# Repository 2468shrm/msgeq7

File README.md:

# msgeq7

A PCB to interface an MSGEQ7 seven channel graphic equalizer IC to my smart sensor platform [link](https://github.com/2468shrm/M4_CAN_Feather_Carrier_v6). The board has a microphone input jack, the MSGEQ7 IC, and three 3-position square pin headers. One header for RESET, one for STROBE, and one for the analog OUTPUT.  These are connected to two DIOs and an AIN, respectively.

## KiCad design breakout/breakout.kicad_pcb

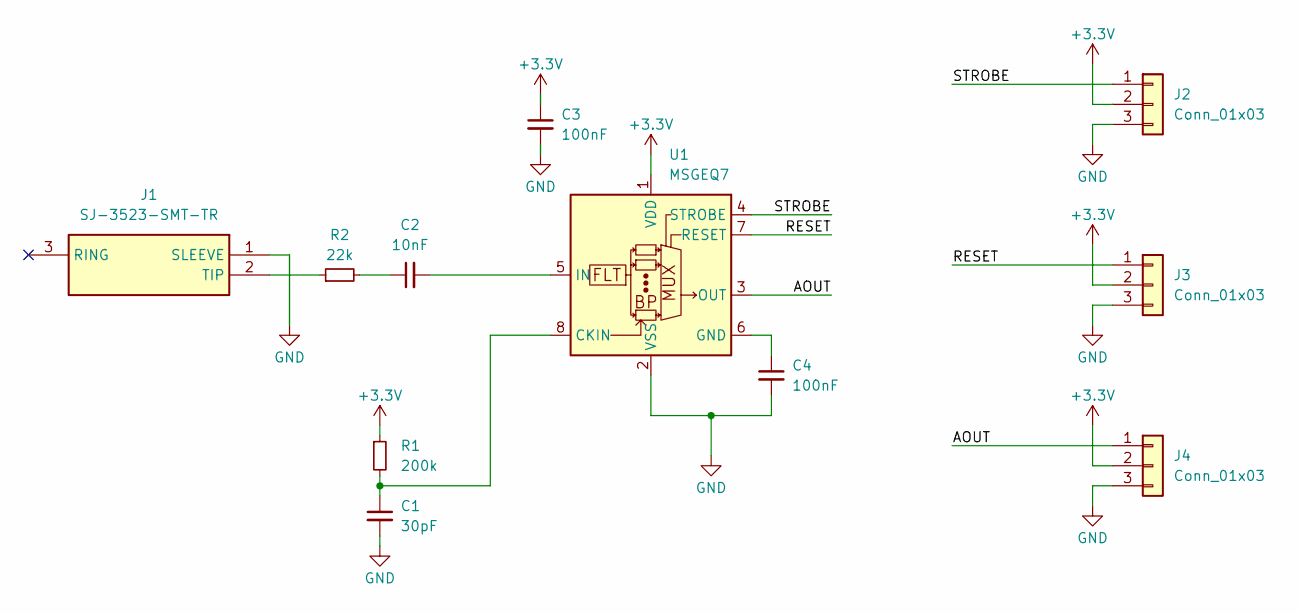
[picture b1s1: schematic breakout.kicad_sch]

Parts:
C1: 30pF; C_0805_2012Metric
C2: 10nF; C_0805_2012Metric
C3, C4: 100nF; C_0805_2012Metric
J1: SJ-3523-SMT-TR; SJ3523SMTTR; Manufacturer_Part_Number SJ-3523-SMT-TR; Mouser Part Number 490-SJ-3523-SMT-TR
J2, J3, J4: Conn_01x03; PinHeader_1x03_P2.54mm_Vertical
R1: 200k; R_0805_2012Metric
R2: 22k; R_0805_2012Metric
U1: MSGEQ7; DIP-8_W7.62mm_LongPads

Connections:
+3.3V: C3.1, J2.2, J3.2, J4.2, R1.1, U1.1 (VDD)
/AOUT: J4.1, U1.3 (OUT)
/RESET: J3.1, U1.7 (RESET)
/STROBE: J2.1, U1.4 (STROBE)
GND: C1.2, C3.2, C4.2, J1.1 (SLEEVE), J2.3, J3.3, J4.3, U1.2 (VSS)
unnamed: C2.1, R2.2
unnamed: J1.2 (TIP), R2.1
unnamed: C1.1, R1.2, U1.8 (CKIN)
unnamed: C4.1, U1.6 (GND)
unnamed: C2.2, U1.5 (IN)

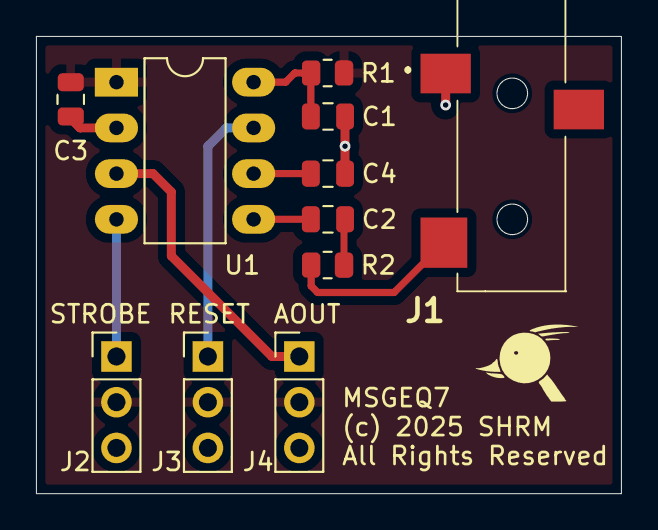
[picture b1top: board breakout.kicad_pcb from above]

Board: 2 copper layers, 32.5 x 25.4 mm, 11 parts (0 on the bottom side), 10 nets.

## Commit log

2025-10-10 KiCAD PCB files
2025-10-10 python module and example, unfinished
2025-10-10 Incremental detail
2025-12-31 includes manufacturing and CAD files plus initial planning notes

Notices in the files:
breakout/breakout.kicad_pcb:
(c) 2025 SHRM
All Rights Reserved
